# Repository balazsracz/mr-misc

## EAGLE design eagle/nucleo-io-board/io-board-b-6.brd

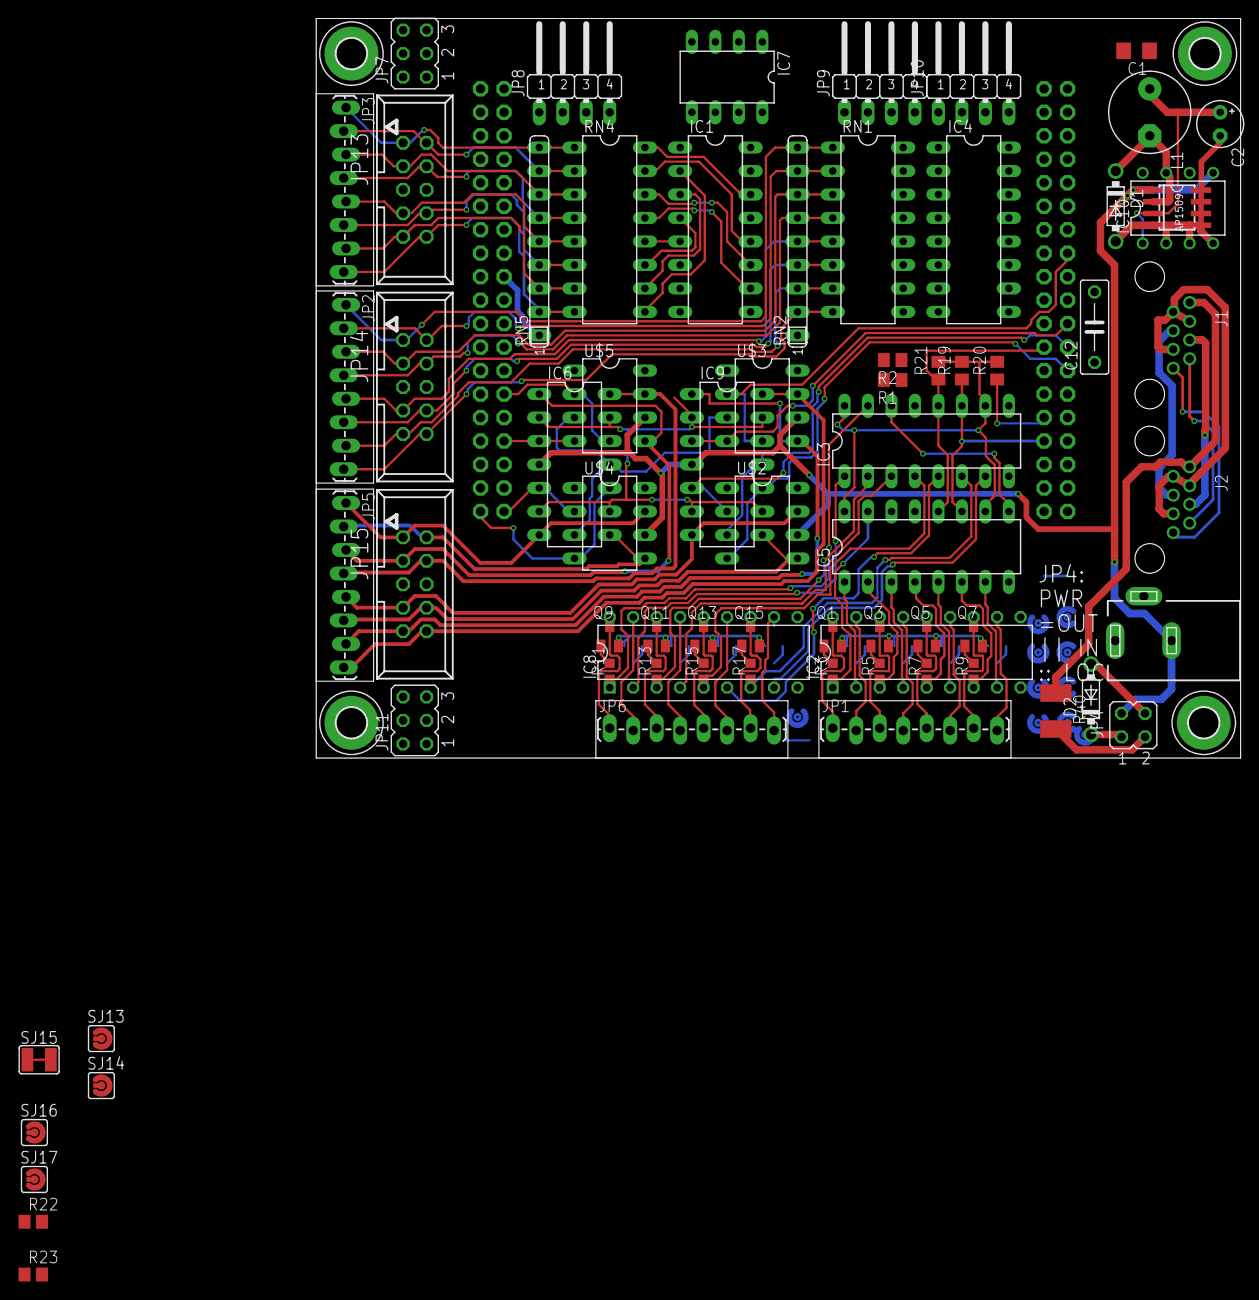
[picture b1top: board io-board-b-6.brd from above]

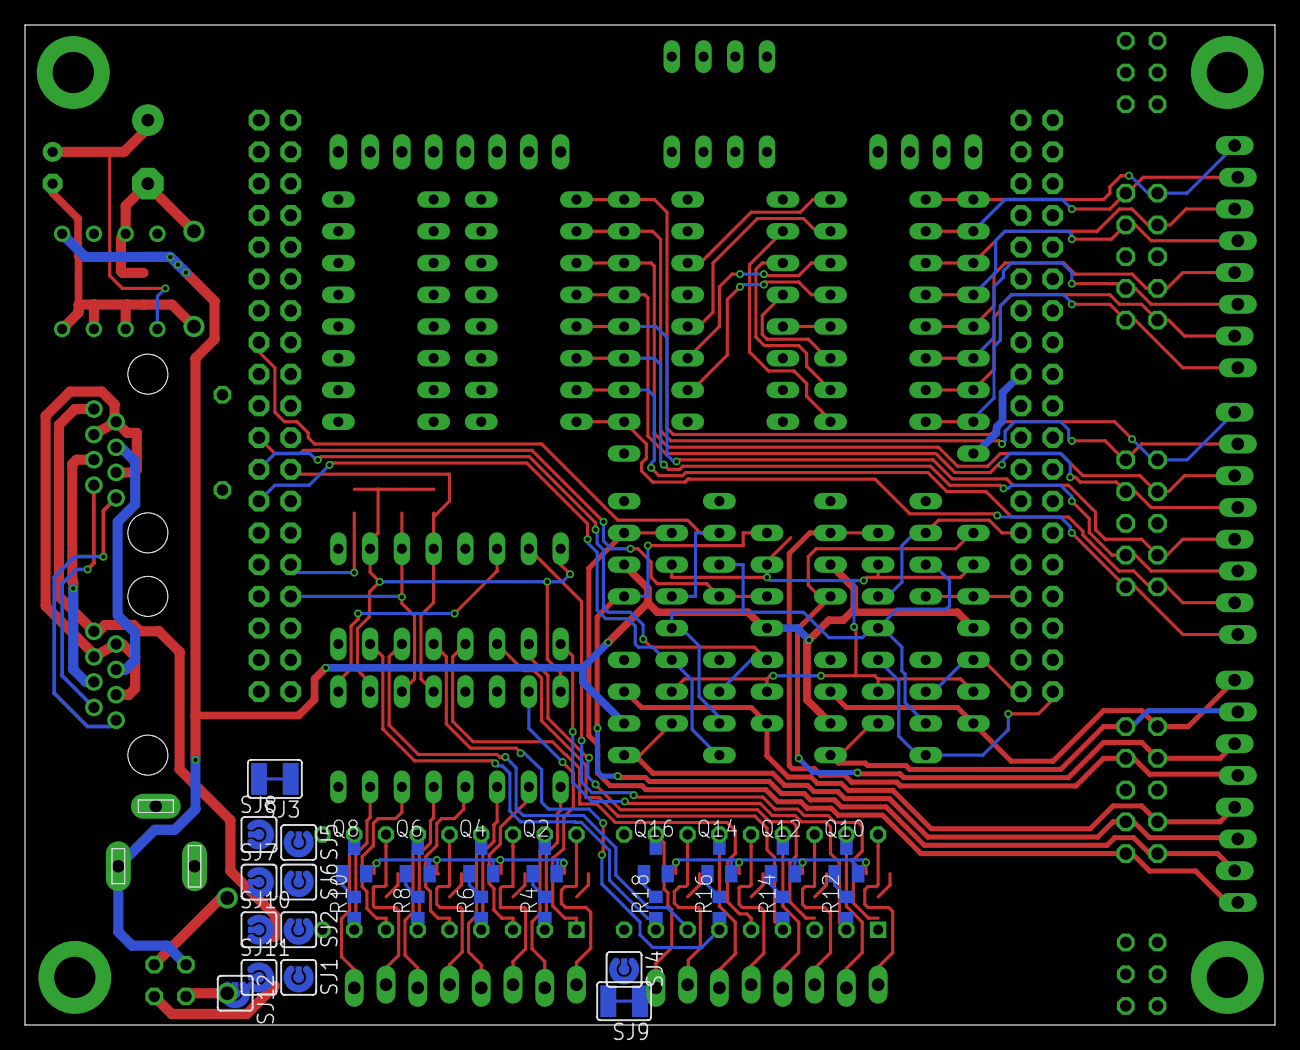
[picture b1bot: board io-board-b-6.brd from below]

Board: 2 copper layers, 100.0 x 80.0 mm, 105 parts (28 on the bottom side), 138 nets.

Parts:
+12V: 9-15V; POWER_USAGE
AP1509: AP1509; SO-08
C1: C1206
C2: E2,5-5
C12: C430C474M5U5TA7200; C075-032X103
D1, D2: DO41-7.6
H1, H2, H3, H4: MOUNT-PAD-ROUND3.3; 3,3-PAD
IC1, IC4: 74166N; DIL16
IC2, IC8: DIL18-THIN
IC3, IC5: 74HCT595N; DIL16
IC6, IC9: LM324N; DIL14
IC7: PCA82C250; DIL08
IC10: LM2574N-5.0; DIL08
J1, J2: RJ45-JACKRJ45-PULSE-E5J00; RJ45-PULSE-E5J88
J3: DCJ0202
JP1, JP2, JP3, JP5, JP6: M08-SCREW; 1X08_TERMINAL
JP4: JP2Q
JP7, JP11: JP3Q
JP8, JP9, JP10: JP4F
JP13, JP14, JP15: CON10M
L1: L-US; L5-8,5
Q1, Q2, Q3, Q4, Q5, Q6, Q7, Q8, Q9, Q10, Q11, Q12, Q13, Q14, Q15, Q16: SOT23
R1, R2: 10k; R0805
R3, R4, R5, R6, R7, R8, R9, R10, R11, R12, R13, R14, R15, R16, R17, R18: R0603
R19, R20, R21, R22, R23: R0805
R40: 0ZCG0035AF2C; PTC1812
RN1, RN4: DIL16
RN2, RN5: 10K; SIL9
SJ1, SJ2, SJ4, SJ5, SJ6, SJ7, SJ8, SJ10, SJ11, SJ12, SJ13, SJ14, SJ16, SJ17: SJ-RND
SJ3, SJ9, SJ15: SJW-C
U$1: NUCLEO_64_GENERIC; NUCLEO_BRD_BASE64
U$2, U$3, U$4, U$5: TC4426APDIP; DIL08-LONG

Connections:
!ISS: IC1.15, IC4.15
+3.3V: IC1.1, IC1.9, IC1.16, IC4.9, IC4.16, IC7.3, R1.2, U$1.3V3
+5V: IC3.10, IC3.16, IC5.10, IC5.16, JP7.3, JP7.4, JP8.3, JP10.2, JP11.3, JP11.4, JP13.6, JP14.6, JP15.6, R19.2, R20.2, R21.2, R22.1, R23.1, RN2.1, RN5.1, SJ1.2, SJ4.2, SJ7.2, SJ10.2, U$1.5V2
+12V: AP1509.1, C12.1, IC6.4, IC9.4, IC10.5, J3.3, JP4.2, JP10.3, SJ2.2, SJ5.2, SJ8.2, SJ11.2, SJ14.2, U$2.6, U$3.6, U$4.6, U$5.6
CANH: IC7.7, J1.1, J2.1
CANL: IC7.6, J1.2, J2.2
CANRX: IC7.4, U$1.PB8
CANTX: IC7.1, U$1.PB9
CMPREF: IC6.2, IC6.6, IC6.9, IC6.13, IC9.2, IC9.6, IC9.9, IC9.13, R1.1, R2.2
E_CS: JP9.4, R23.2, U$1.PC10
E_LAT: JP10.1, R22.2, U$1.PC11
E_MOSI: JP9.2, SJ15.2, SJ16.2
GND: AP1509.4, AP1509.5, AP1509.6, AP1509.7, AP1509.8, C1.2, C2.-, C12.2, D1.A, IC1.6, IC1.8, IC3.8, IC3.13, IC4.6, IC4.8, IC5.8, IC5.13, IC6.11, IC7.2, IC9.11, IC10.2, IC10.3, IC10.4, J1.3, J1.6, J1.7, J2.3, J2.6, J2.7, J3.1, JP7.5, JP7.6, JP8.4, JP10.4, JP11.5, JP11.6, JP13.5, JP14.5, JP15.5, Q1.2, Q2.2, Q3.2, Q4.2, Q5.2, Q6.2, Q7.2, Q8.2, Q9.2, Q10.2, Q11.2, Q12.2, Q13.2, Q14.2, Q15.2, Q16.2, R2.1, SJ3.2, SJ6.2, SJ9.2, SJ12.2, U$1.GND3, U$1.GND4, U$1.GND5, U$1.GND6, U$1.GND7, U$1.GND8, U$2.3, U$3.3, U$4.3, U$5.3
I2CSCL: JP8.2, U$1.PB6
I2CSDA: JP8.1, U$1.PB7
MISO: JP9.1, U$1.PB4
MISO2: IC4.13, SJ13.2, U$1.PC2
MOSI: IC5.14, R20.1, SJ15.1, SJ17.2, U$1.PB5
unnamed: IC2.1, IC5.15, R3.1
unnamed: IC2.18, JP1.1, Q1.3
unnamed: IC2.2, IC5.1, R4.1
unnamed: J1.4, J2.4
unnamed: J1.5, J2.5
unnamed: JP3.8, JP13.10, RN4.8, RN5.2
unnamed: IC2.17, JP1.2, Q2.3
unnamed: IC2.3, IC5.2, R5.1
unnamed: IC2.16, JP1.3, Q3.3
unnamed: IC2.4, IC5.3, R6.1
unnamed: IC2.15, JP1.4, Q4.3
unnamed: IC2.5, IC5.4, R7.1
unnamed: IC2.14, JP1.5, Q5.3
unnamed: JP3.7, JP13.9, RN4.7, RN5.3
unnamed: JP3.6, JP13.8, RN4.6, RN5.4
unnamed: Q4.1, R6.2
unnamed: IC2.6, IC5.5, R8.1
unnamed: IC2.13, JP1.6, Q6.3
unnamed: JP3.4, JP13.4, RN4.4, RN5.6
unnamed: JP3.3, JP13.3, RN4.3, RN5.7
unnamed: JP2.6, JP14.8, RN1.6, RN2.4
unnamed: JP3.1, JP13.1, RN4.1, RN5.9
unnamed: IC1.2, RN4.9
unnamed: IC1.3, RN4.10
unnamed: JP2.8, JP14.10, RN1.8, RN2.2
unnamed: JP2.7, JP14.9, RN1.7, RN2.3
unnamed: Q5.1, R7.2
unnamed: JP2.5, JP14.7, RN1.5, RN2.5
unnamed: IC1.4, RN4.11
unnamed: IC1.5, RN4.12
unnamed: IC1.10, RN4.13
unnamed: IC1.11, RN4.14
unnamed: JP2.4, JP14.4, RN1.4, RN2.6
unnamed: JP2.3, JP14.3, RN1.3, RN2.7
unnamed: JP2.2, JP14.2, RN1.2, RN2.8
unnamed: JP2.1, JP14.1, RN1.1, RN2.9
unnamed: IC1.12, RN4.15
unnamed: IC1.14, RN4.16
unnamed: IC2.7, IC5.6, R9.1
unnamed: IC2.12, JP1.7, Q7.3
unnamed: IC2.8, IC5.7, R10.1
unnamed: IC2.11, JP1.8, Q8.3
unnamed: Q6.1, R8.2
unnamed: IC4.2, RN1.9
unnamed: D2.C, JP4.1
unnamed: D2.A, JP4.4
unnamed: IC4.3, RN1.10
unnamed: IC4.4, RN1.11
unnamed: IC4.5, RN1.12
unnamed: IC4.10, RN1.13
unnamed: IC4.11, RN1.14
unnamed: IC4.12, RN1.15
unnamed: IC4.14, RN1.16
unnamed: IC2.9, SJ1.1, SJ2.1, SJ3.1
unnamed: IC2.10, SJ4.1, SJ5.1, SJ6.1
unnamed: IC3.15, IC8.1, R11.1
unnamed: JP4.3, R40.2
unnamed: SJ13.1, U$1.PB14
unnamed: IC1.13, IC4.1
unnamed: SJ14.1, U$1.VIN2
unnamed: Q7.1, R9.2
unnamed: IC8.11, JP6.8, Q16.3
unnamed: IC8.9, SJ7.1, SJ8.1, SJ9.1
unnamed: IC8.10, SJ10.1, SJ11.1, SJ12.1
unnamed: Q1.1, R3.2
unnamed: Q2.1, R4.2
unnamed: JP3.5, JP13.7, RN4.5, RN5.5
unnamed: JP3.2, JP13.2, RN4.2, RN5.8
unnamed: Q8.1, R10.2
unnamed: IC8.18, JP6.1, Q9.3
unnamed: Q3.1, R5.2
unnamed: IC3.1, IC8.2, R12.1
unnamed: IC8.17, JP6.2, Q10.3
unnamed: IC3.2, IC8.3, R13.1
unnamed: IC8.16, JP6.3, Q11.3
unnamed: IC3.3, IC8.4, R14.1
unnamed: IC8.15, JP6.4, Q12.3
unnamed: IC3.4, IC8.5, R15.1
unnamed: IC8.14, JP6.5, Q13.3
unnamed: IC3.5, IC8.6, R16.1
unnamed: IC8.13, JP6.6, Q14.3
unnamed: IC3.6, IC8.7, R17.1
unnamed: IC8.12, JP6.7, Q15.3
unnamed: IC3.7, IC8.8, R18.1
unnamed: Q9.1, R11.2
unnamed: Q10.1, R12.2
unnamed: Q11.1, R13.2
unnamed: Q12.1, R14.2
unnamed: Q13.1, R15.2
unnamed: Q14.1, R16.2
unnamed: Q15.1, R17.2
unnamed: Q16.1, R18.2
OLAT: IC3.12, IC5.12, R21.1, U$1.PA8
PWR_POS: J1.8, J2.8, R40.1
SCK: IC3.11, IC5.11, JP9.3, R19.1, U$1.PB3
SCK2: IC1.7, IC4.7, U$1.PB10
SLNK1: IC3.14, IC5.9, SJ17.1
SLNK2: IC3.9, SJ16.1
SRV1: JP7.2, U$1.PC9
SRV2: JP7.1, U$1.PC7
SRV3: JP11.2, U$1.PC8
SRV4: JP11.1, U$1.PC6
SW: AP1509.2, D1.C, IC10.7, L1.2
TIN1: IC9.3, U$1.PB2, U$3.4
TIN2: IC9.5, U$1.PB1, U$2.2
TIN3: IC9.10, U$1.PB15, U$2.4
TIN4: IC9.12, U$1.PB12, U$3.2
TIN5: IC6.3, U$1.PA4, U$5.4
TIN6: IC6.5, U$1.PC0, U$4.2
TIN7: IC6.10, U$1.PC3, U$4.4
TIN8: IC6.12, U$1.PA0, U$5.2
TOUT1: IC6.7, JP5.1, JP15.1, U$4.7
TOUT2: IC6.8, JP5.2, JP15.2, U$4.5
TOUT3: IC6.1, JP5.3, JP15.3, U$5.5
TOUT4: IC6.14, JP5.4, JP15.4, U$5.7
TOUT5: IC9.7, JP5.5, JP15.7, U$2.7
TOUT6: IC9.8, JP5.6, JP15.8, U$2.5
TOUT7: IC9.1, JP5.7, JP15.9, U$3.5
TOUT8: IC9.14, JP5.8, JP15.10, U$3.7
V+: AP1509.3, C1.1, C2.+, IC10.1, L1.1, U$1.E5V
